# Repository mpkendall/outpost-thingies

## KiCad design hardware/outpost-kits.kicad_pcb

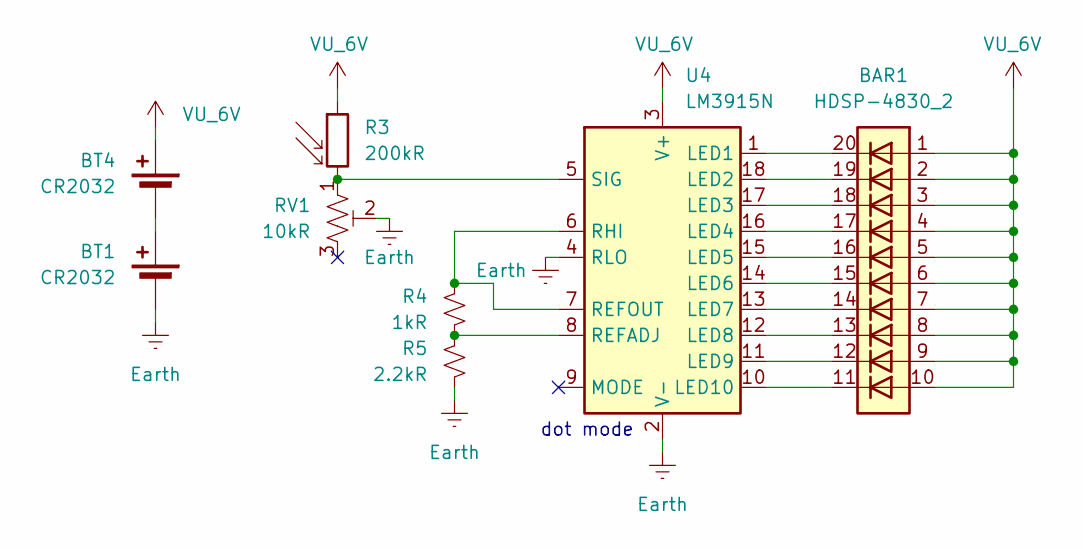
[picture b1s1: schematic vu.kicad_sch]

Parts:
BAR1: HDSP-4830_2; HDSP-48xx; DIGIKEY 160-1067-ND
BT1, BT4: CR2032; BatteryHolder_Keystone_103_1x20mm; LCSC C70376
R3: 200kR; R_LDR_5.1x4.3mm_P3.4mm_Vertical; LCSC C10077
R4: 1kR; R_Axial_DIN0204_L3.6mm_D1.6mm_P5.08mm_Horizontal; LCSC C2896955
R5: 2.2kR; R_Axial_DIN0204_L3.6mm_D1.6mm_P5.08mm_Horizontal; LCSC C2896997
RV1: 10kR; Potentiometer_ACP_CA9-H5_Horizontal; LCSC C5205021
U4: LM3915N; DIP-18_W7.62mm; LCSC C55109574

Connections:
Earth: BT1.2 (-), R5.1, RV1.2, U4.2 (V-), U4.4 (RLO); also elsewhere on the board
unnamed: BT1.1 (+), BT4.2 (-)
unnamed: BAR1.20 (K), U4.1 (LED1)
unnamed: BAR1.19 (K), U4.18 (LED2)
unnamed: BAR1.18 (K), U4.17 (LED3)
unnamed: BAR1.17 (K), U4.16 (LED4)
unnamed: BAR1.16 (K), U4.15 (LED5)
unnamed: BAR1.15 (K), U4.14 (LED6)
unnamed: BAR1.14 (K), U4.13 (LED7)
unnamed: BAR1.13 (K), U4.12 (LED8)
unnamed: BAR1.12 (K), U4.11 (LED9)
unnamed: BAR1.11 (K), U4.10 (LED10)
unnamed: R4.1, R5.2, U4.8 (REFADJ)
unnamed: R4.2, U4.6 (RHI), U4.7 (REFOUT)
unnamed: R3.2, RV1.1, U4.5 (SIG)
VU_6V: BAR1.1 (A), BAR1.2 (A), BAR1.3 (A), BAR1.4 (A), BAR1.5 (A), BAR1.6 (A), BAR1.7 (A), BAR1.8 (A), BAR1.9 (A), BAR1.10 (A), BT4.1 (+), R3.1, U4.3 (V+)

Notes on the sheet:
dot mode

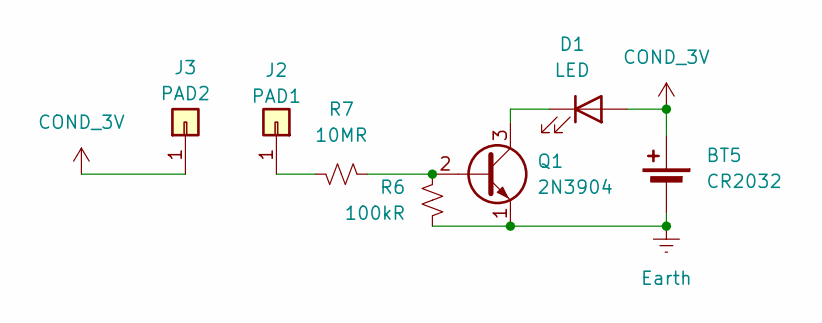
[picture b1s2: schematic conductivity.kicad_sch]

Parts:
BT5: CR2032; BatteryHolder_Keystone_103_1x20mm; LCSC C70376
D1: LED; LED_D5.0mm_FlatTop; LCSC C52034661
J2: PAD1
J3: PAD2
Q1: 2N3904; TO-92_Inline; LCSC C2874602
R6: 100kR; R_Axial_DIN0204_L3.6mm_D1.6mm_P5.08mm_Horizontal; LCSC C2848520
R7: 10MR; R_Axial_DIN0204_L3.6mm_D1.6mm_P5.08mm_Horizontal; LCSC C2896925

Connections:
COND_3V: BT5.1 (+), D1.2 (A), J3.1
Earth: BT5.2 (-), Q1.1 (E), R6.1; also elsewhere on the board
unnamed: D1.1 (K), Q1.3 (C)
unnamed: Q1.2 (B), R6.2, R7.1
unnamed: J2.1, R7.2

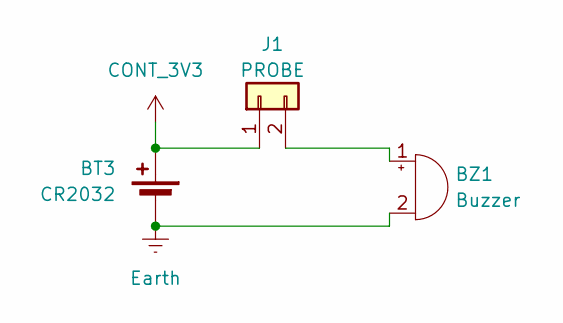
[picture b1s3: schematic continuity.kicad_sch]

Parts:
BT3: CR2032; BatteryHolder_Keystone_103_1x20mm; LCSC C70376
BZ1: Buzzer; Buzzer_12x9.5RM7.6; LCSC C49246930
J1: PROBE; PinSocket_1x02_P2.54mm_Vertical

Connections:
CONT_3V3: BT3.1 (+), J1.1
Earth: BT3.2 (-), BZ1.2 (-); also elsewhere on the board
unnamed: BZ1.1 (+), J1.2

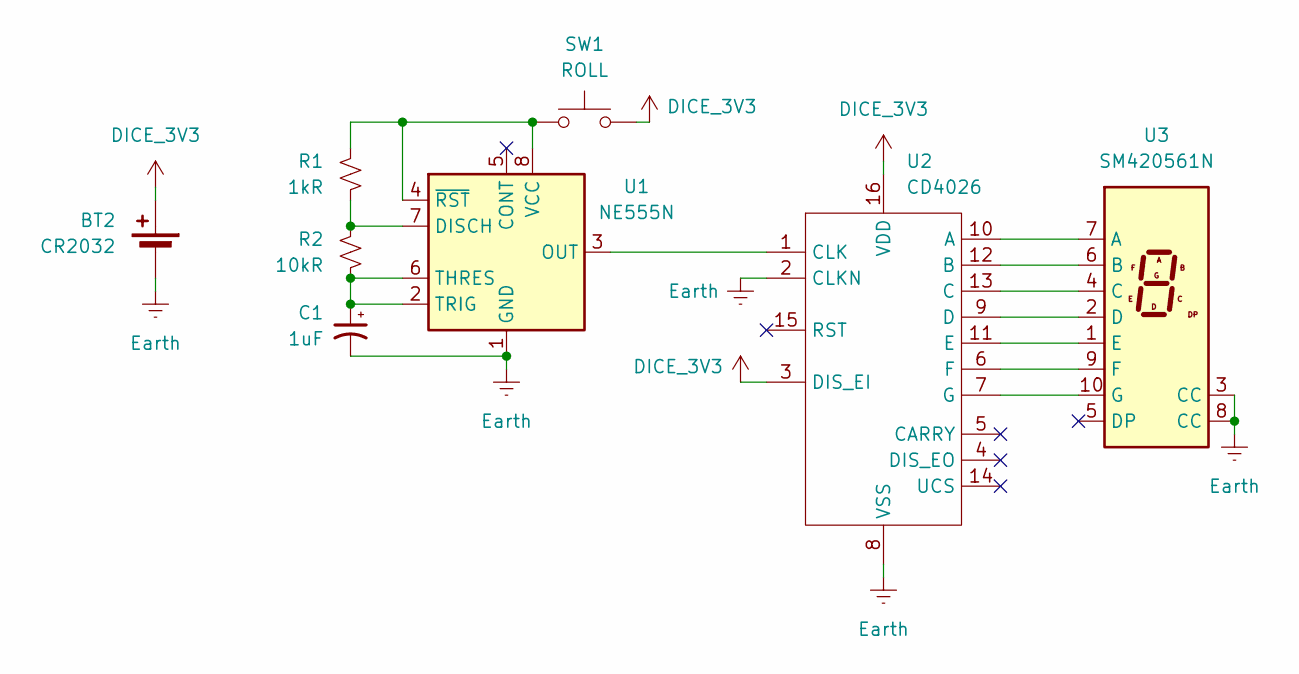
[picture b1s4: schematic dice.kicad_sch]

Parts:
BT2: CR2032; BatteryHolder_Keystone_103_1x20mm; LCSC C70376
C1: 1uF; CP_Radial_D5.0mm_P2.00mm; LCSC C49304893
R1: 1kR; R_Axial_DIN0204_L3.6mm_D1.6mm_P5.08mm_Horizontal; LCSC C2896955
R2: 10kR; R_Axial_DIN0204_L3.6mm_D1.6mm_P5.08mm_Horizontal; LCSC C2896924
SW1: ROLL; SW_PUSH_6mm; LCSC C52750873
U1: NE555N; DIP-8_W7.62mm; LCSC C510566
U2: CD4026; DIP-16_W7.62mm; LCSC C51912176
U3: SM420561N; 7SegmentLED_LTS6760_LTS6780; LCSC C141367

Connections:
DICE_3V3: BT2.1 (+), SW1.2, U2.3 (DIS_EI), U2.16 (VDD)
Earth: BT2.2 (-), C1.2, U1.1 (GND), U2.2 (CLKN), U2.8 (VSS), U3.3 (CC), U3.8 (CC); also elsewhere on the board
unnamed: R1.1, R2.2, U1.7 (DISCH)
unnamed: U1.3 (OUT), U2.1 (CLK)
unnamed: C1.1, R2.1, U1.2 (TRIG), U1.6 (THRES)
unnamed: R1.2, SW1.1, U1.4 (~RST), U1.8 (VCC)
unnamed: U2.10 (A), U3.7 (A)
unnamed: U2.12 (B), U3.6 (B)
unnamed: U2.13 (C), U3.4 (C)
unnamed: U2.9 (D), U3.2 (D)
unnamed: U2.11 (E), U3.1 (E)
unnamed: U2.6 (F), U3.9 (F)
unnamed: U2.7 (G), U3.10 (G)

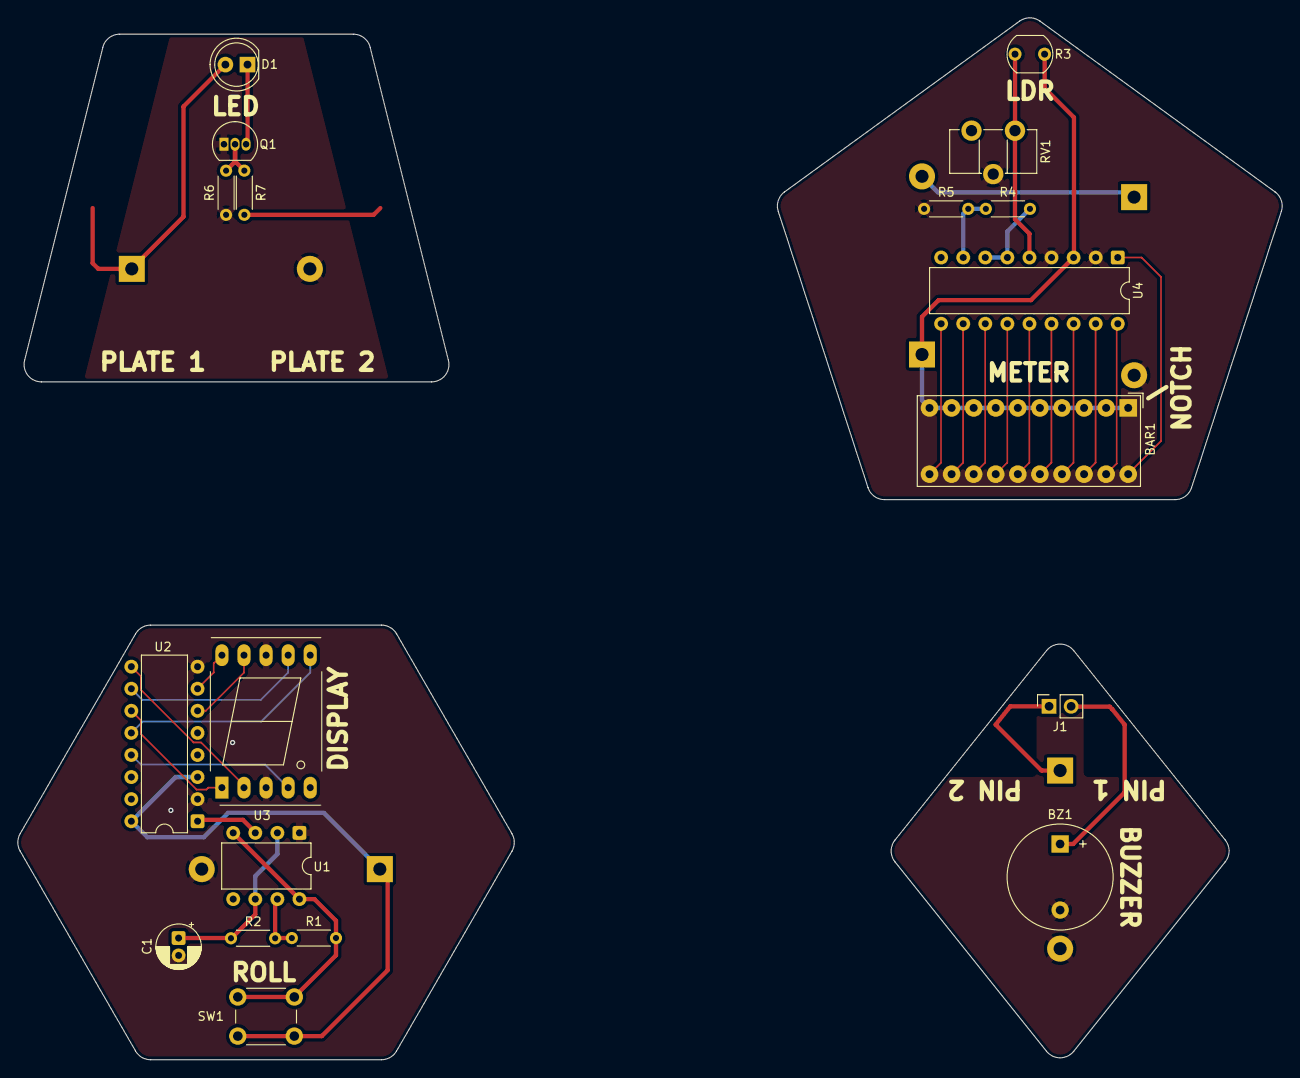
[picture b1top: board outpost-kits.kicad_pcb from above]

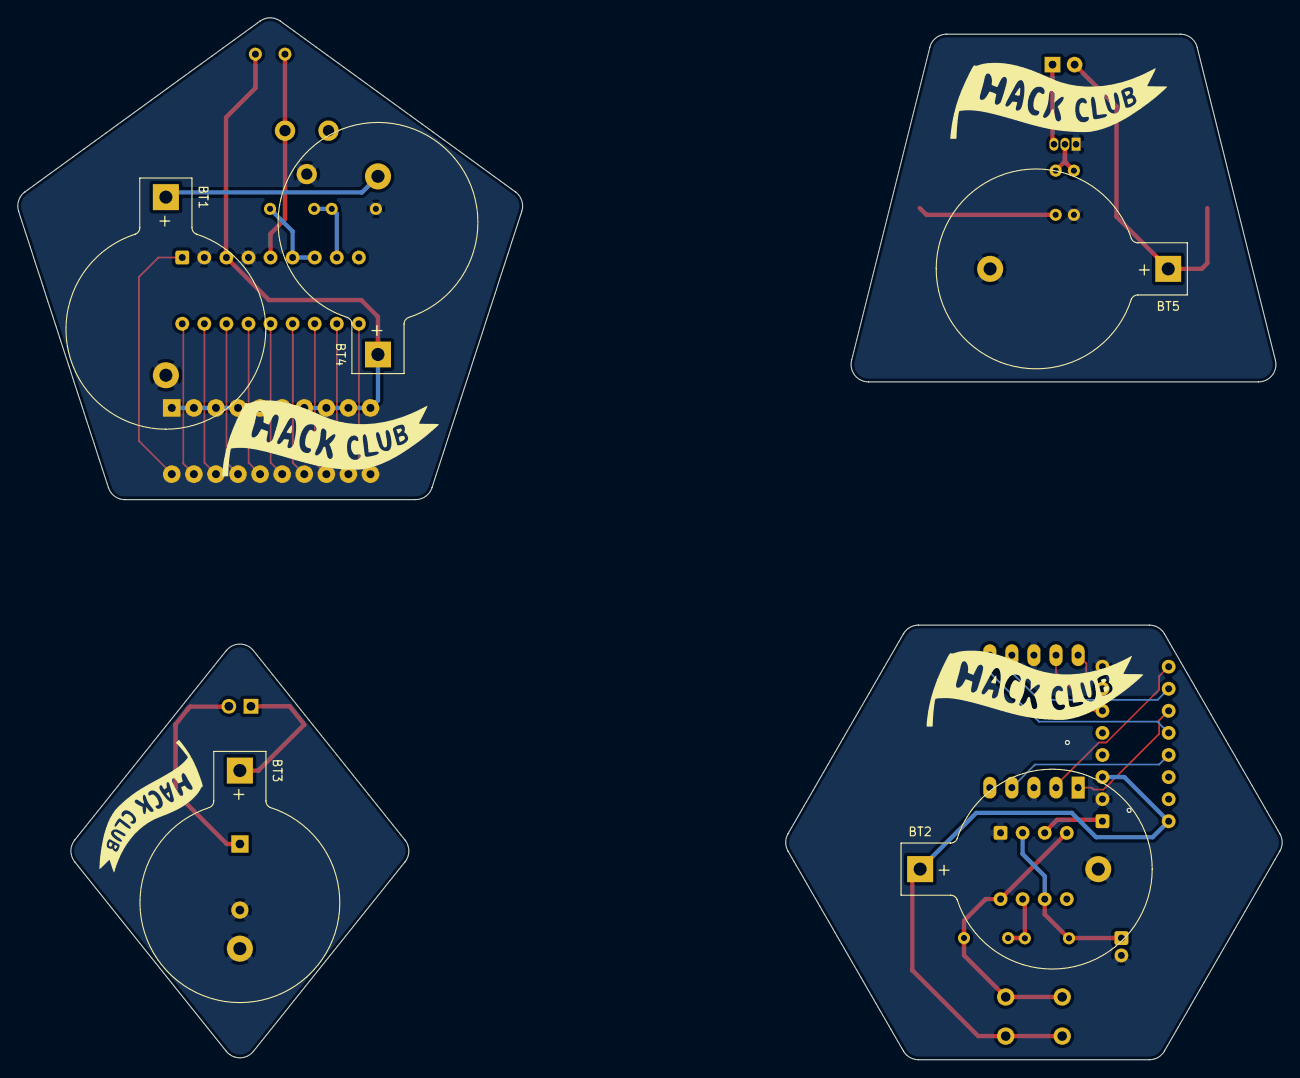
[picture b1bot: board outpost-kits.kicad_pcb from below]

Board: 2 copper layers, 145.5 x 119.9 mm, 24 parts (5 on the bottom side), 33 nets.

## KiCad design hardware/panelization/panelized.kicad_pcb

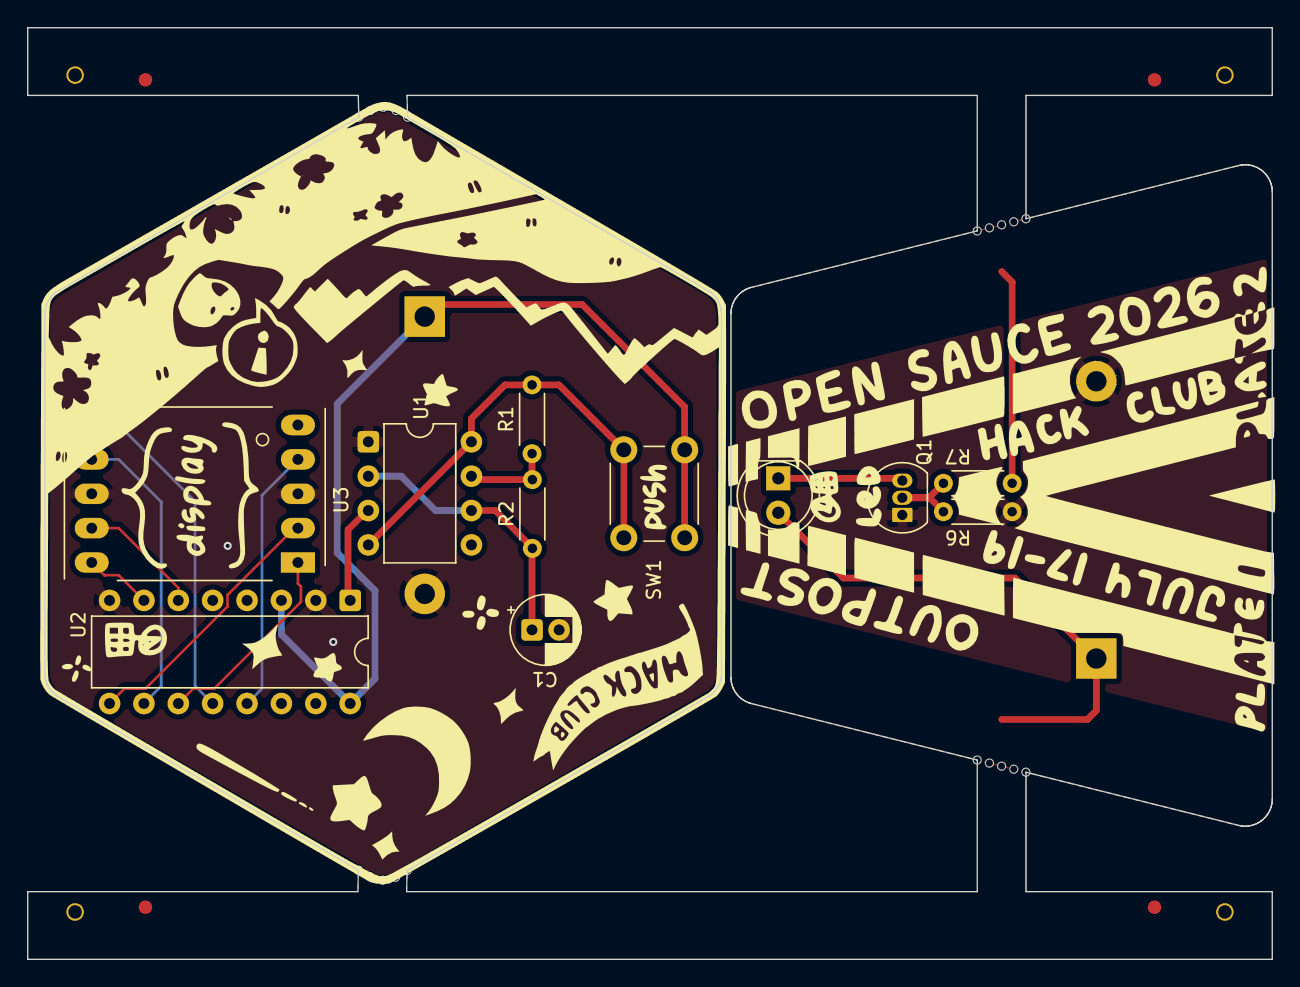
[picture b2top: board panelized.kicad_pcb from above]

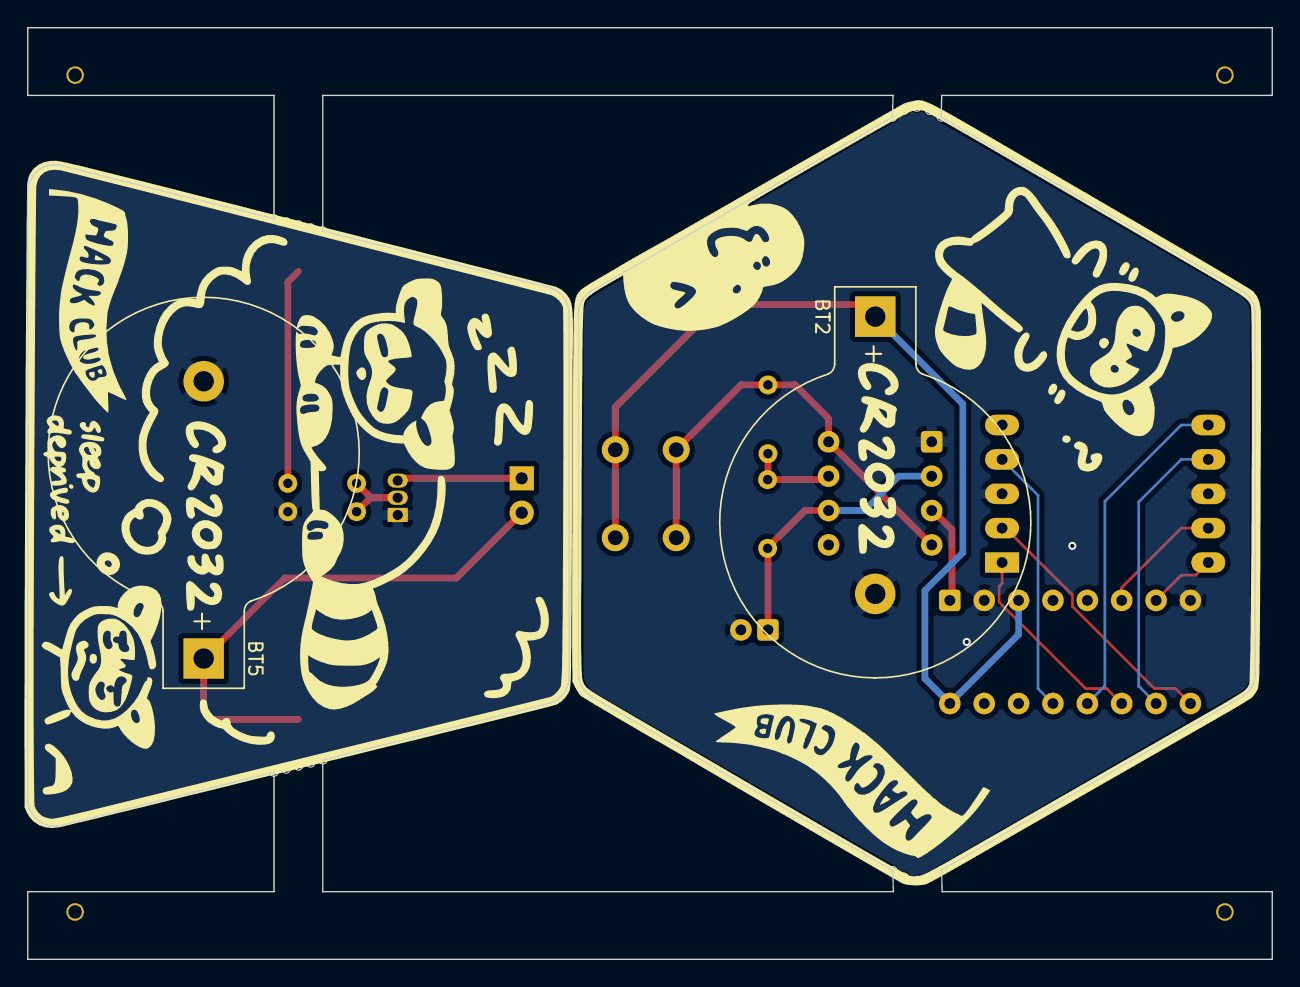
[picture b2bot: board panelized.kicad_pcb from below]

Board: 2 copper layers, 92.0 x 68.8 mm, 37 parts (4 on the bottom side), 17 nets.

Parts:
B0-BT5, B1-BT2: CR2032; BatteryHolder_Keystone_103_1x20mm
B0-D1: LED; LED_D5.0mm_FlatTop
B0-G***, B0-G***#2, B1-G***, B1-G***#2: LOGO
B0-Q1: 2N3904; TO-92_Inline
B0-R6: 100kR; R_Axial_DIN0204_L3.6mm_D1.6mm_P5.08mm_Horizontal
B0-R7: 10MR; R_Axial_DIN0204_L3.6mm_D1.6mm_P5.08mm_Horizontal
B1-C1: 1uF; CP_Radial_D5.0mm_P2.00mm
B1-R1: 1kR; R_Axial_DIN0204_L3.6mm_D1.6mm_P5.08mm_Horizontal
B1-R2: 10kR; R_Axial_DIN0204_L3.6mm_D1.6mm_P5.08mm_Horizontal
B1-SW1: ROLL; SW_PUSH_6mm
B1-U1: NE555N; DIP-8_W7.62mm
B1-U2: CD4026; DIP-16_W7.62mm
B1-U3: SM420561N; 7SegmentLED_LTS6760_LTS6780
KiKit_MB_1_1, KiKit_MB_1_2, KiKit_MB_1_3, KiKit_MB_1_4, KiKit_MB_1_5, KiKit_MB_2_1, KiKit_MB_2_2, KiKit_MB_2_3, KiKit_MB_2_4, KiKit_MB_2_5, KiKit_MB_3_1, KiKit_MB_3_2, KiKit_MB_3_3, KiKit_MB_3_4, KiKit_MB_3_5, KiKit_MB_4_1, KiKit_MB_4_2, KiKit_MB_4_3, KiKit_MB_4_4, KiKit_MB_4_5: NPTH

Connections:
B0-COND_3V: B0-BT5.1 (+), B0-D1.2 (A)
B0-Earth: B0-BT5.2 (-), B0-Q1.1 (E), B0-R6.1
B0-Net-(D1-K): B0-D1.1 (K), B0-Q1.3 (C)
B0-Net-(Q1-B): B0-Q1.2 (B), B0-R6.2, B0-R7.1
B1-DICE_3V3: B1-BT2.1 (+), B1-SW1.2, B1-U2.3 (DIS_EI), B1-U2.16 (VDD)
B1-Earth: B1-BT2.2 (-), B1-C1.2, B1-U1.1 (GND), B1-U2.2 (CLKN), B1-U2.8 (VSS), B1-U3.3 (CC), B1-U3.8 (CC)
B1-Net-(U1-DISCH): B1-R1.1, B1-R2.2, B1-U1.7 (DISCH)
B1-Net-(U1-OUT): B1-U1.3 (OUT), B1-U2.1 (CLK)
B1-Net-(U1-THRES): B1-C1.1, B1-R2.1, B1-U1.2 (TRIG), B1-U1.6 (THRES)
B1-Net-(U1-VCC): B1-R1.2, B1-SW1.1, B1-U1.4 (~RST), B1-U1.8 (VCC)
B1-Net-(U2-A): B1-U2.10 (A), B1-U3.7 (A)
B1-Net-(U2-B): B1-U2.12 (B), B1-U3.6 (B)
B1-Net-(U2-C): B1-U2.13 (C), B1-U3.4 (C)
B1-Net-(U2-D): B1-U2.9 (D), B1-U3.2 (D)
B1-Net-(U2-E): B1-U2.11 (E), B1-U3.1 (E)
B1-Net-(U2-F): B1-U2.6 (F), B1-U3.9 (F)
B1-Net-(U2-G): B1-U2.7 (G), B1-U3.10 (G)
